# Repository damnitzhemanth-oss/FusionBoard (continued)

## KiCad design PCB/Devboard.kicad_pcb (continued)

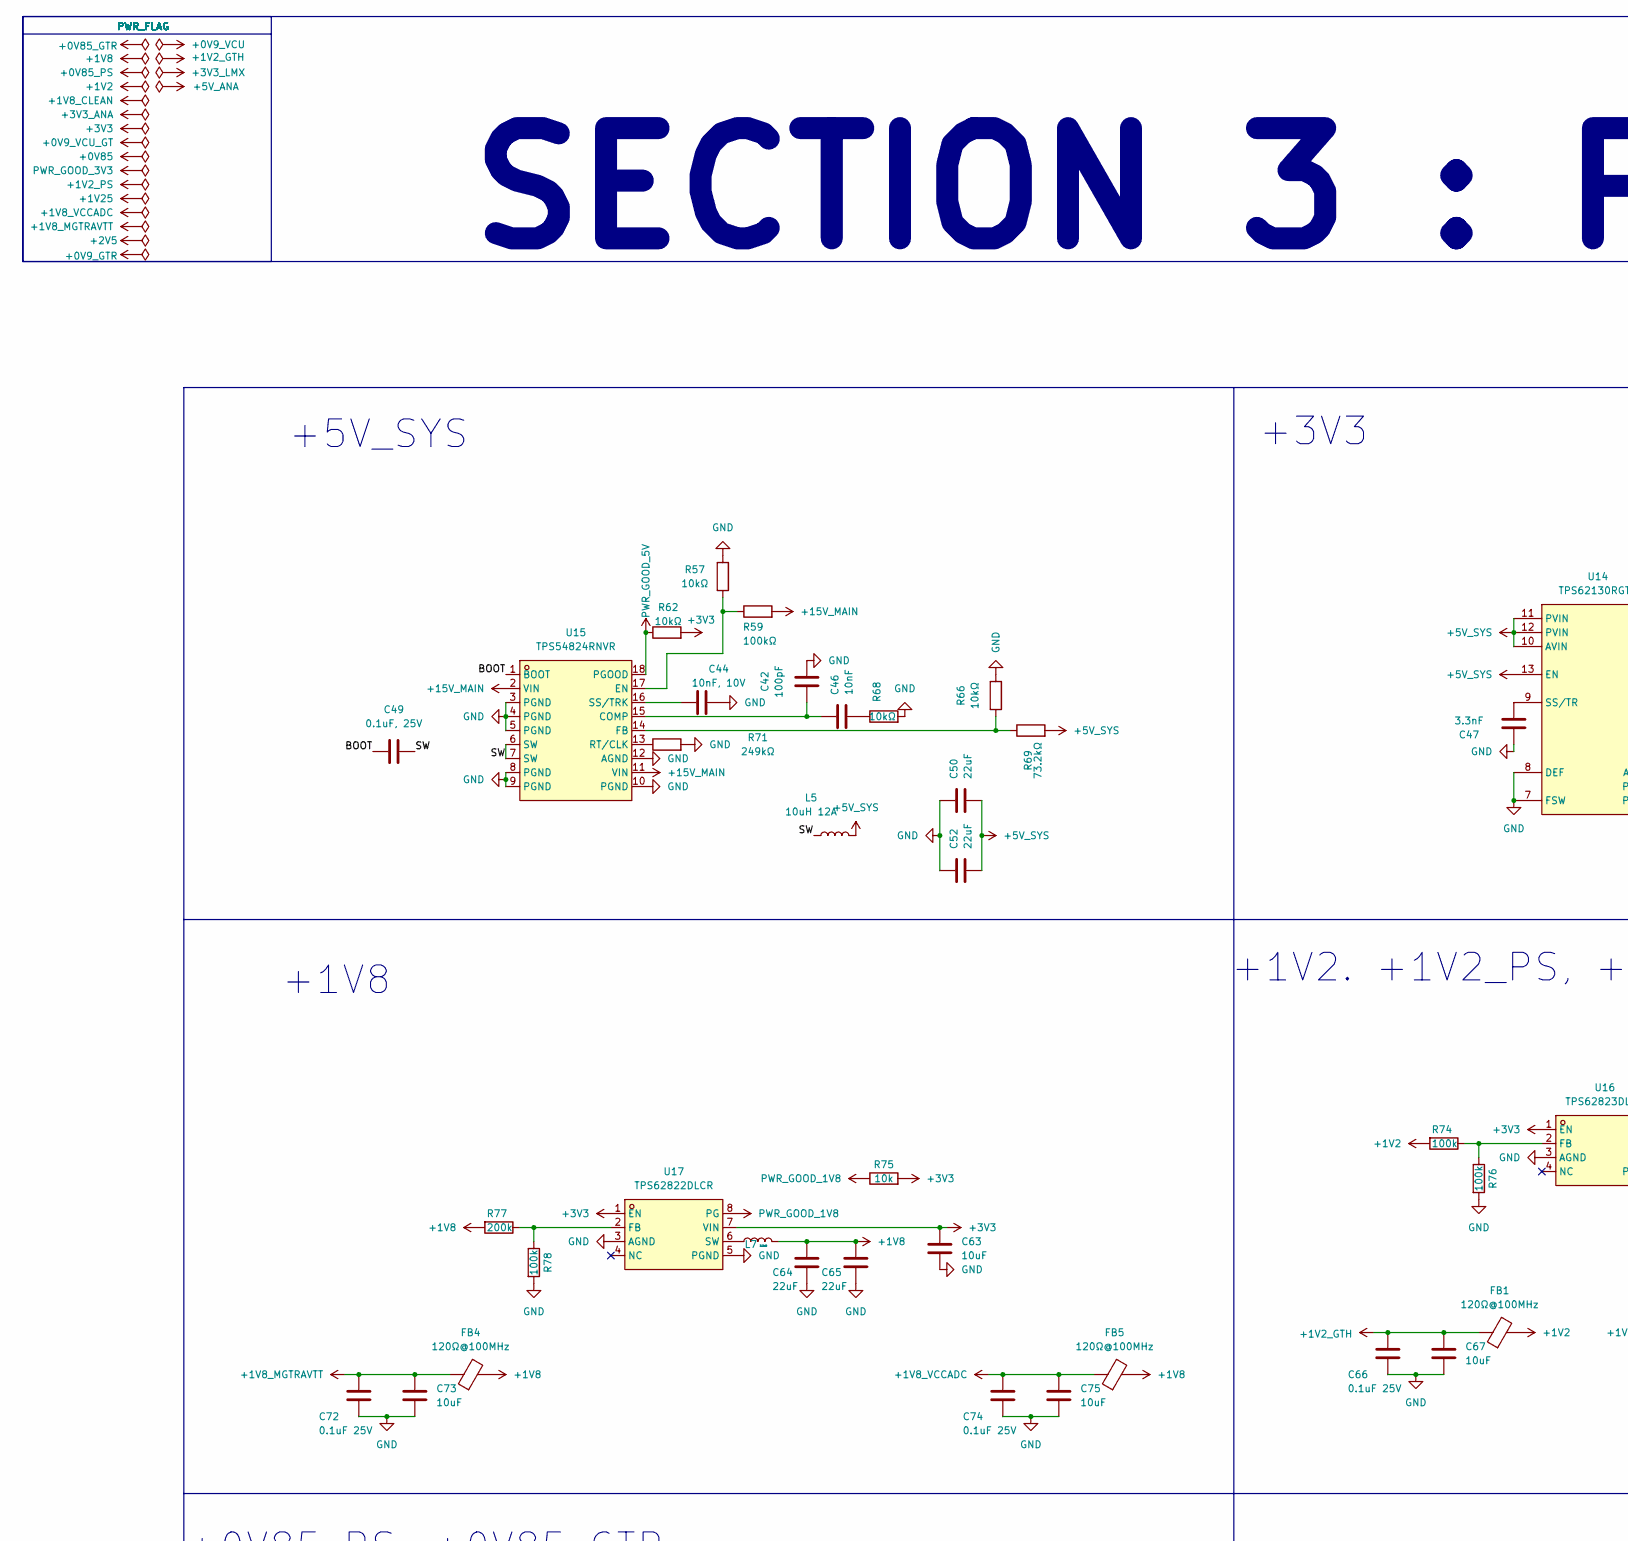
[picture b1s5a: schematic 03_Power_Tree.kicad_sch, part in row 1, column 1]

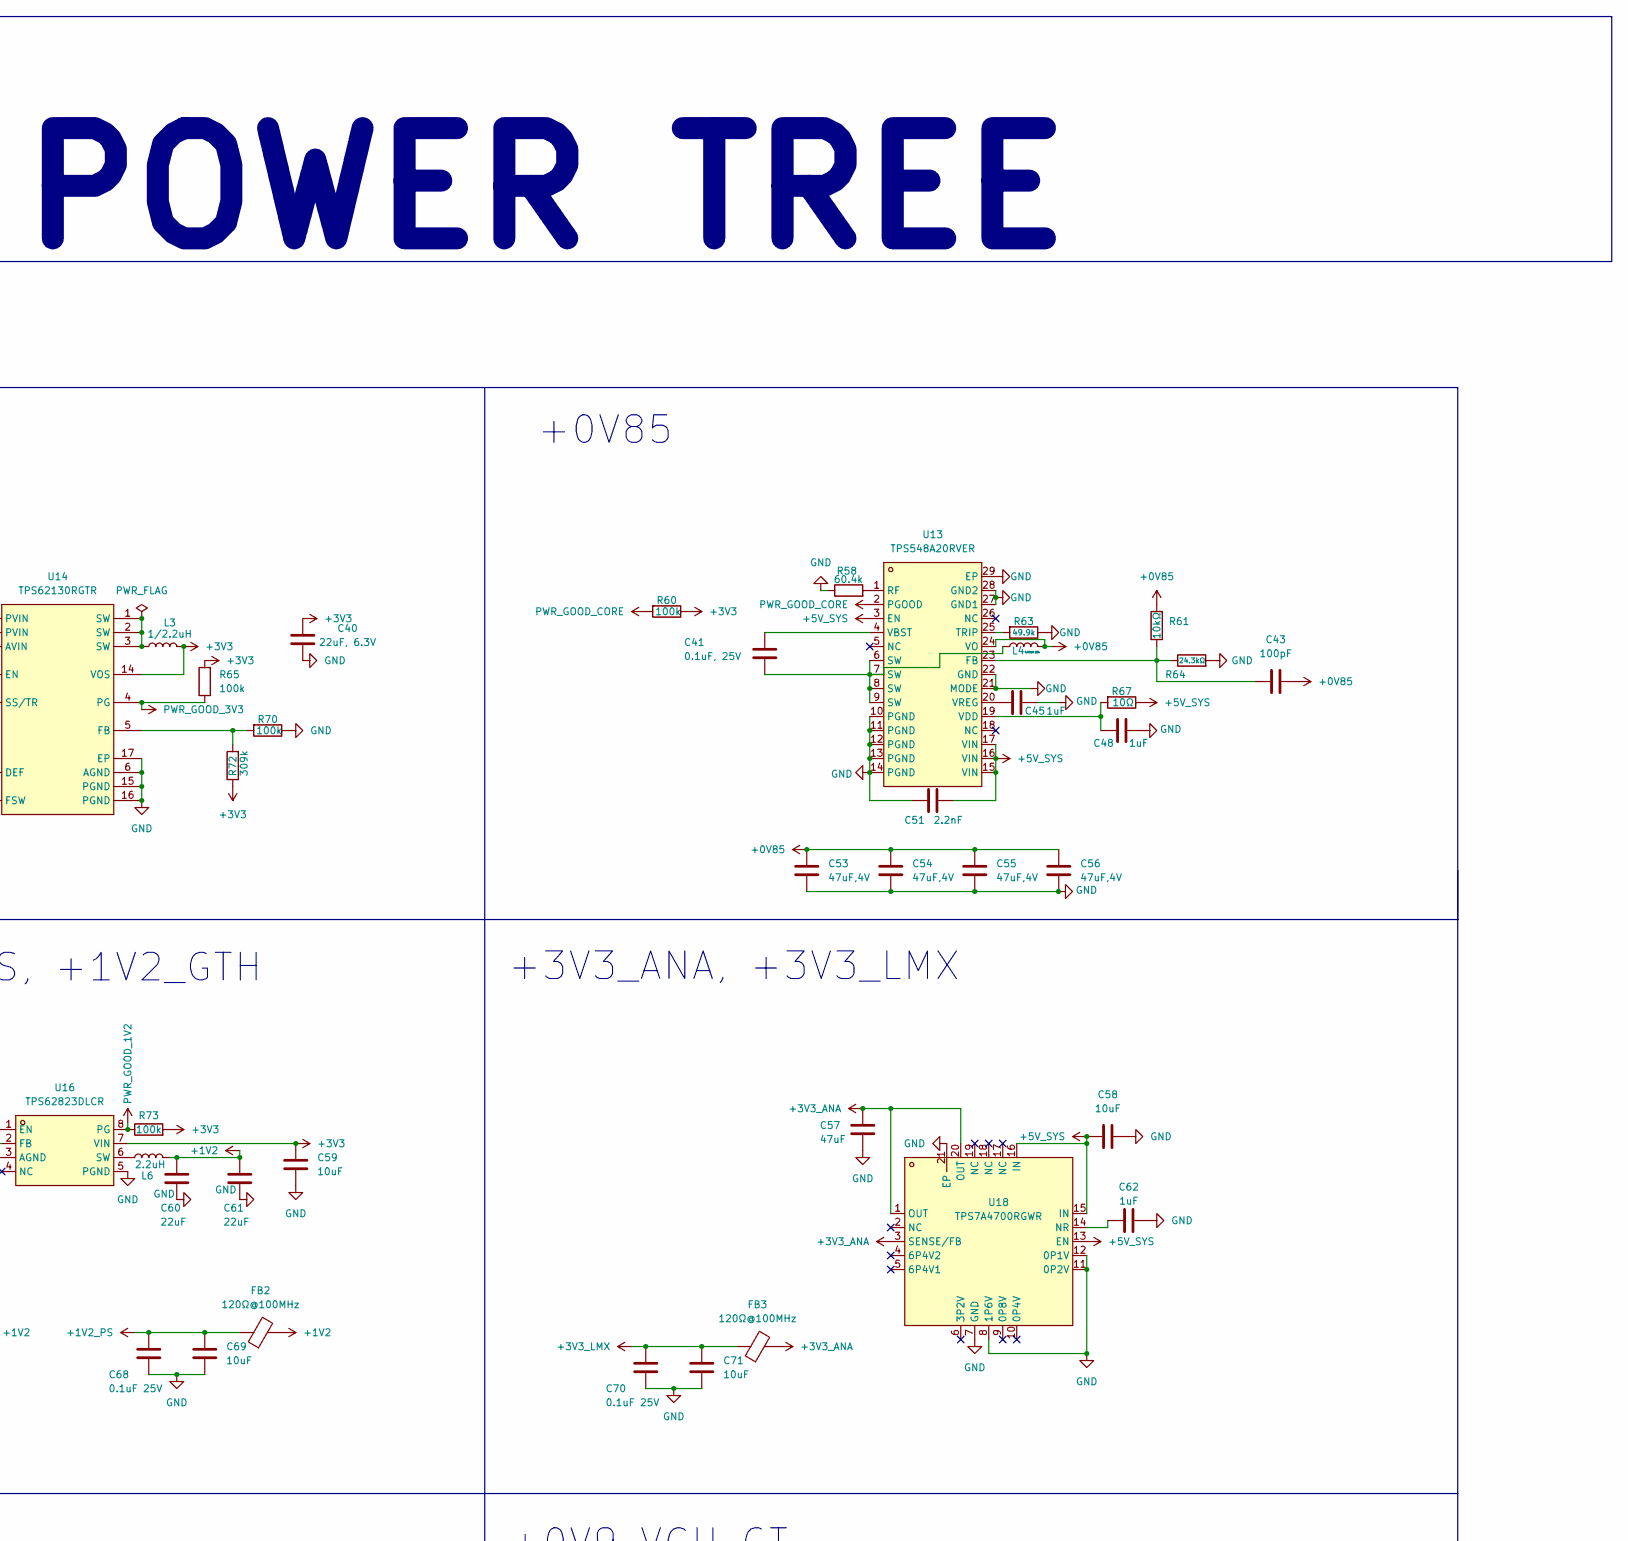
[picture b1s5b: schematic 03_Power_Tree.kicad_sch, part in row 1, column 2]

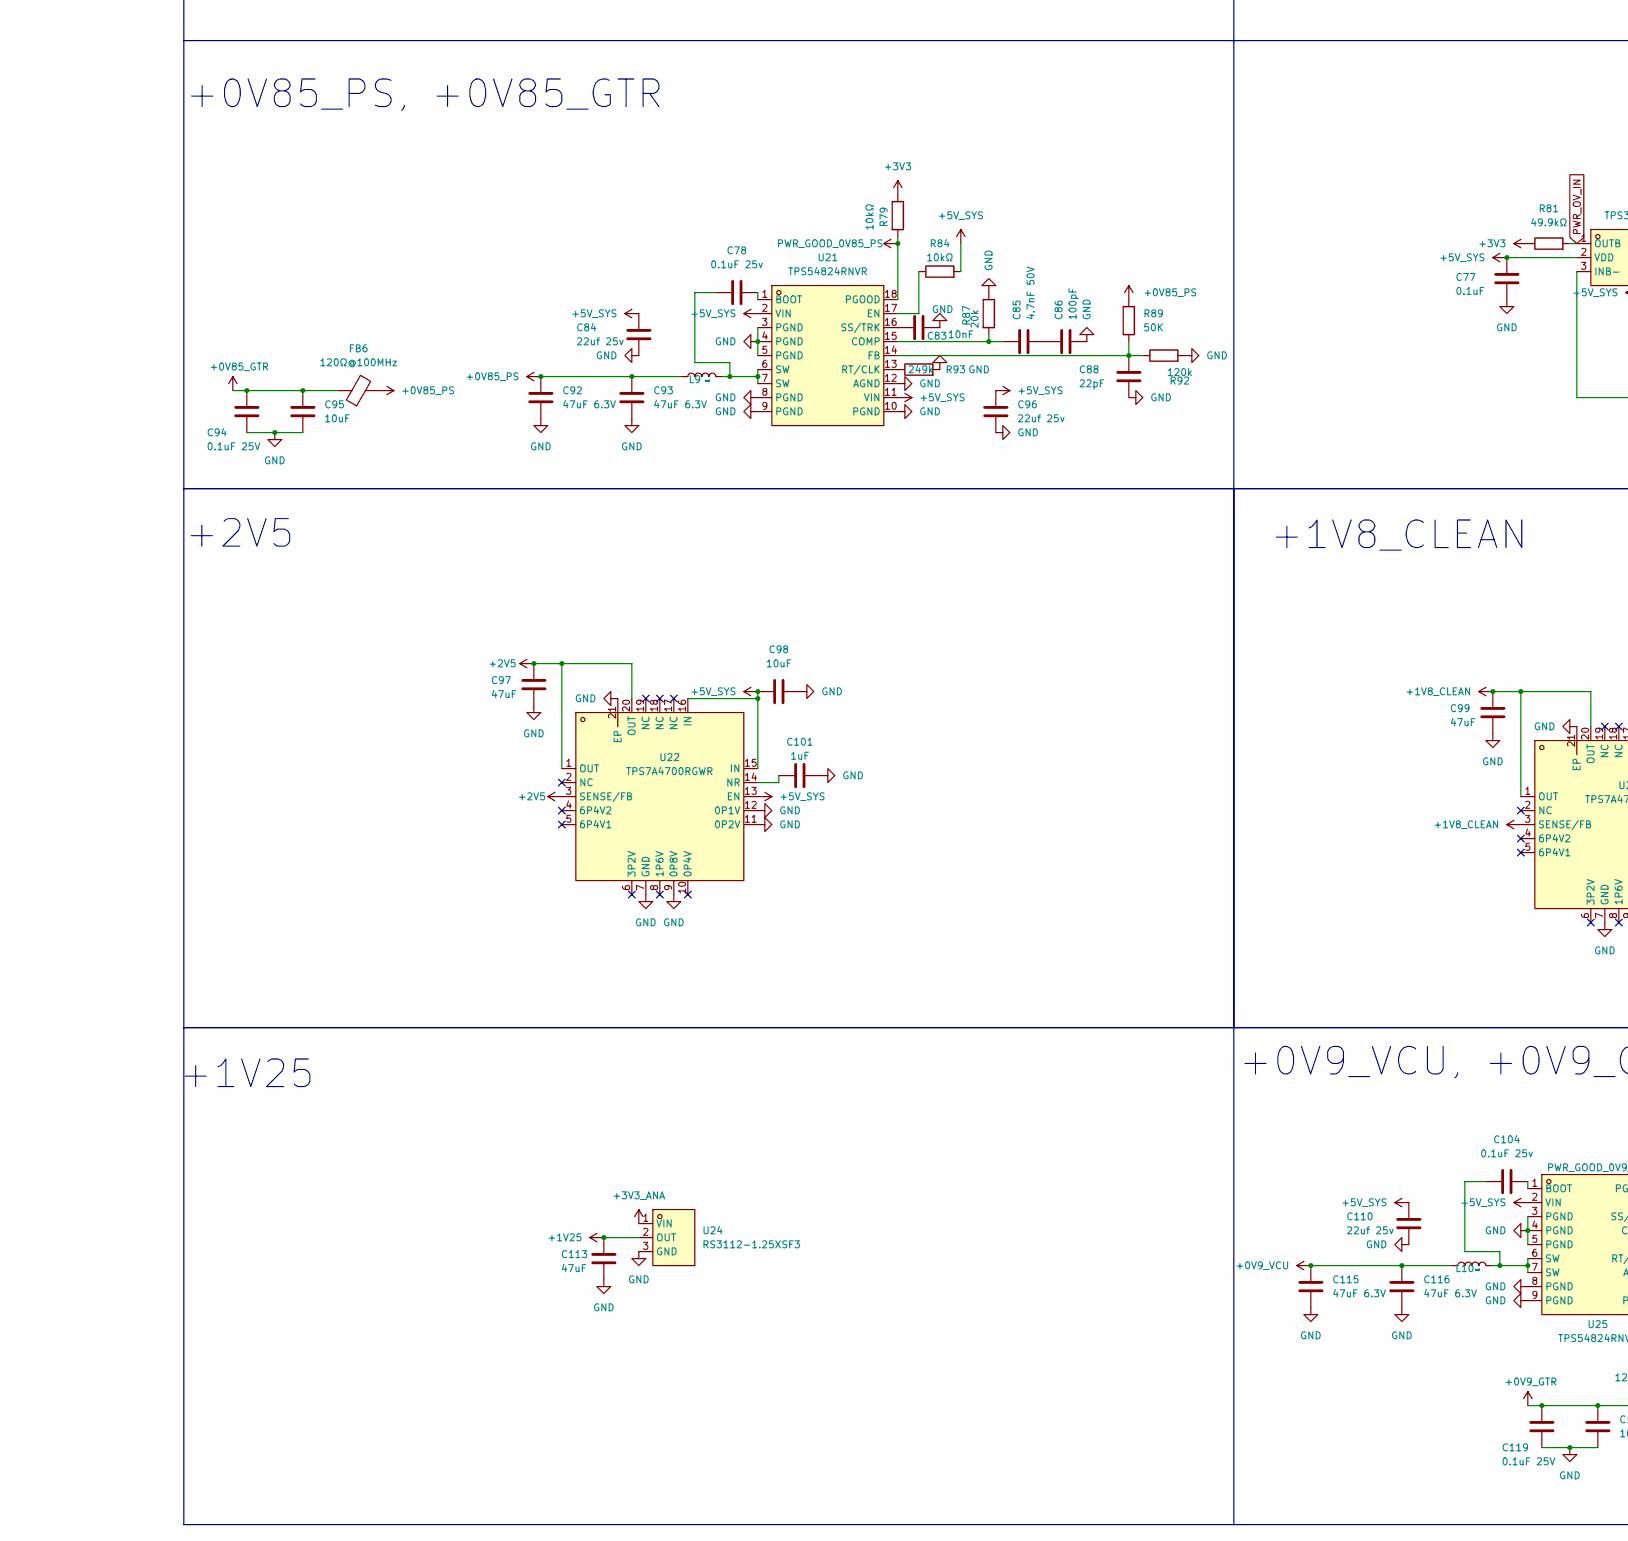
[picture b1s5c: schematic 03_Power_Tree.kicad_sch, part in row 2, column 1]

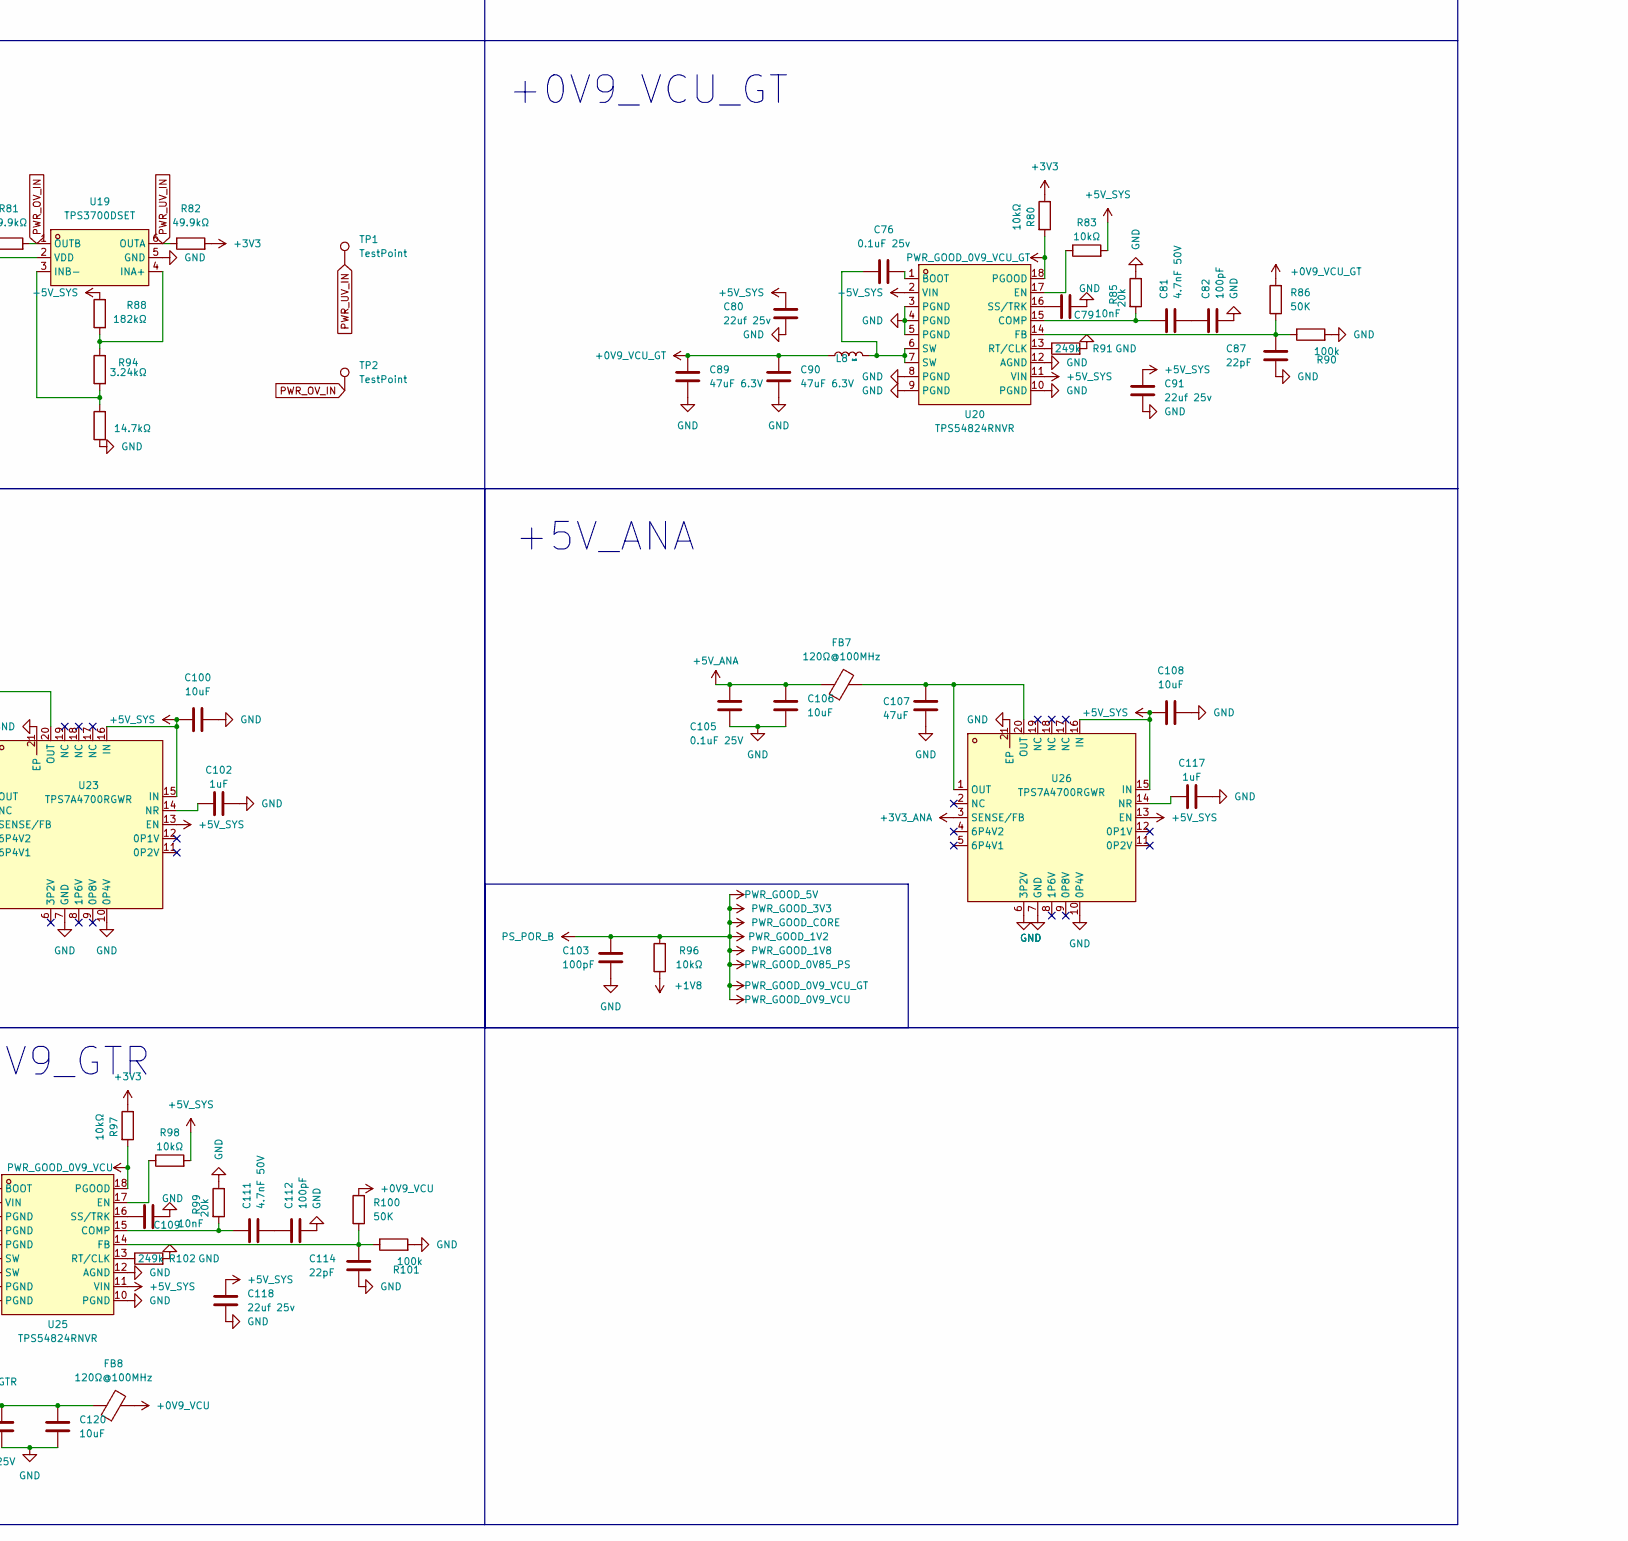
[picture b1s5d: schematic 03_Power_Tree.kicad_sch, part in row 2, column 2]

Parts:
C40: 22uF, 6.3V; C_0805_2012Metric
C41, C49: 0.1uF, 25V; C_0402_1005Metric
C42, C43, C82, C86, C103, C112: 100pF; C_0402_1005Metric
C44: 10nF, 10V; C_0402_1005Metric
C45, C48, C62, C101, C102, C117: 1uF; C_0402_1005Metric
C46, C79, C83, C109: 10nF; C_0402_1005Metric
C47: 3.3nF; C_0402_1005Metric
C50, C52, C60, C61, C64, C65: 22uF; C_0805_2012Metric
C51: 2.2nF; C_0402_1005Metric
C53, C54, C55, C56: 47uF,4V; C_1206_3216Metric
C57, C97, C99, C107, C113: 47uF; C_1206_3216Metric
C58, C59, C63, C67, C69, C71, C73, C75, C95, C98, C100, C106, C108, C120: 10uF; C_0402_1005Metric
C66, C68, C70, C72, C74, C94, C105, C119: 0.1uF 25V; C_0402_1005Metric
C76, C78, C104: 0.1uF 25v; C_0402_1005Metric
C77: 0.1uF; C_0402_1005Metric
C80, C84, C91, C96, C110, C118: 22uf 25v; C_0805_2012Metric
C81, C85, C111: 4.7nF 50V; C_0402_1005Metric
C87, C88, C114: 22pF; C_0402_1005Metric
C89, C90, C92, C93, C115, C116: 47uF 6.3V; C_1206_3216Metric
FB1, FB2, FB3, FB4, FB5, FB6, FB7, FB8: 120Ω@100MHz; L_01005_0402Metric
L3: 1/2.2uH; L_Bourns_SRP1245A
L4: 0.47uH 15A; L_Bourns_SRP1245A
L5: 10uH 12A; L_Bourns_SRP1245A
L6, L7: 2.2uH; L_Bourns_SRP1245A
L8, L9, L10: 1uH; L_Bourns_SRP1245A
R57, R61, R62, R66, R68, R79, R80, R83, R84, R96, R97, R98: 10kΩ; R_0402_1005Metric
R58: 60.4k; R_0402_1005Metric
R59: 100kΩ; R_0402_1005Metric
R60, R65, R70, R73, R74, R76, R78, R90, R101: 100k; R_0402_1005Metric
R63: 49.9k; R_0402_1005Metric
R64: 24.3kΩ; R_0402_1005Metric
R67: 10Ω; R_0402_1005Metric
R69: 73.2kΩ; R_0402_1005Metric
R71: 249kΩ; R_0402_1005Metric
R72: 309k; R_0402_1005Metric
R75: 10k; R_0402_1005Metric
R77: 200k; R_0402_1005Metric
R81, R82: 49.9kΩ; R_0402_1005Metric
R85, R87, R99: 20k; R_0402_1005Metric
R86, R89, R100: 50K; R_0402_1005Metric
R88: 182kΩ; R_0402_1005Metric
R91, R93, R102: 249k; R_0402_1005Metric
R92: 120k; R_0402_1005Metric
R94: 3.24kΩ; R_0402_1005Metric
R95: 14.7kΩ; R_0402_1005Metric
TP1, TP2: TestPoint; TestPoint_Pad_D1.0mm
U13: TPS548A20RVER; VQFN-CLIP-28_L4.5-W3.5-P0.40-BL-EP; MPN TPS548A20RVER; LCSC Part C468255
U14: TPS62130RGTR; QFN-16_L3.0-W3.0-P0.50-TL-EP1.7; MPN TPS62130RGTR; LCSC Part C43590
U15, U20, U21, U25: TPS54824RNVR; VQFN-18_L3.5-W3.5-P0.50-BL_TPS54824RNVR; MPN TPS54824RNVR; LCSC Part C2070614
U16: TPS62823DLCR; VSON-8_L2.0-W1.5-P0.50-BL; MPN TPS62823DLCR; LCSC Part C2693497
U17: TPS62822DLCR; VSON-8_L2.0-W1.5-P0.50-BL; MPN TPS62822DLCR; LCSC Part C473385
U18, U22, U23, U26: TPS7A4700RGWR; VQFN-20_L5.0-W5.0-P0.65-TL-EP; MPN TPS7A4700RGWR; LCSC Part C114839
U19: TPS3700DSET; WSON-6_L1.5-W1.5-P0.50-TL; MPN TPS3700DSET; LCSC Part C2869244
U24: RS3112-1.25XSF3; SOT-23-3_L2.9-W1.3-P0.95-LS2.4-BR; MPN RS3112-1.25XSF3; LCSC Part C19269195

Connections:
+0V9_GTR: C119.1, C120.2, FB8.1; also elsewhere on the board
+0V9_VCU: C115.1, C116.1, FB8.2, L10.1, R100.2; also elsewhere on the board
+0V9_VCU_GT: C89.1, C90.1, L8.1, R86.2; also elsewhere on the board
+0V85: C43.2, C53.1, C54.1, C55.1, C56.1, L4.2, R61.2, U13.24 (VO); also elsewhere on the board
+0V85_GTR: C94.1, C95.2, FB6.1; also elsewhere on the board
+0V85_PS: C92.1, C93.1, FB6.2, L9.1, R89.2; also elsewhere on the board
+1V2: C60.1, C61.1, FB1.2, FB2.2, L6.2, R74.2; also elsewhere on the board
+1V2_GTH: C66.1, C67.2, FB1.1; also elsewhere on the board
+1V2_PS: C68.1, C69.2, FB2.1; also elsewhere on the board
+1V8: C64.1, C65.1, FB4.2, FB5.2, L7.2, R77.2, R96.1; also elsewhere on the board
+1V8_CLEAN: C99.1, U23.1 (OUT), U23.3 (SENSE/FB), U23.20 (OUT); also elsewhere on the board
+1V8_MGTRAVTT: C72.1, C73.2, FB4.1; also elsewhere on the board
+1V8_VCCADC: C74.1, C75.2, FB5.1; also elsewhere on the board
+1V25: C113.1, U24.2 (OUT); also elsewhere on the board
+2V5: C97.1, U22.1 (OUT), U22.3 (SENSE/FB), U22.20 (OUT); also elsewhere on the board
+3V3: C40.1, C59.1, C63.1, L3.2, R60.1, R62.2, R65.2, R72.1, R73.2, R75.2, R79.1, R80.1, R81.1, R82.2, R97.1, U14.14 (VOS), U16.1 (EN), U16.7 (VIN), U17.1 (EN), U17.7 (VIN); also elsewhere on the board
+3V3_ANA: C57.1, FB3.2, U18.1 (OUT), U18.3 (SENSE/FB), U18.20 (OUT), U24.1 (VIN), U26.3 (SENSE/FB); also elsewhere on the board
+3V3_LMX: C70.1, C71.2, FB3.1; also elsewhere on the board
+5V_ANA: C105.1, C106.2, FB7.1; also elsewhere on the board
+5V_SYS: C50.2, C51.2, C52.2, C58.1, C77.1, C80.1, C84.1, C91.1, C96.1, C98.1, C100.1, C108.1, C110.1, C118.1, L5.2, R67.1, R69.2, R83.2, R84.2, R88.1, R98.2, U13.3 (EN), U13.15 (VIN), U13.16 (VIN), U13.17 (VIN), U14.10 (AVIN), U14.11 (PVIN), U14.12 (PVIN), U14.13 (EN), U18.13 (EN), U18.15 (IN), U18.16 (IN), U19.2 (VDD), U20.2 (VIN), U20.11 (VIN), U21.2 (VIN), U21.11 (VIN), U22.13 (EN), U22.15 (IN), U22.16 (IN), U23.13 (EN), U23.15 (IN), U23.16 (IN), U25.2 (VIN), U25.11 (VIN), U26.13 (EN), U26.15 (IN), U26.16 (IN); also elsewhere on the board
+15V_MAIN: R59.2, U15.2 (VIN), U15.11 (VIN); also elsewhere on the board
/Power Tree/BOOT: C49.1, U15.1 (BOOT)
/Power Tree/SW: C49.2, L5.1, U15.6 (SW), U15.7 (SW)
GND: C40.2, C42.2, C44.2, C45.2, C47.1, C48.2, C50.1, C51.1, C52.1, C53.2, C54.2, C55.2, C56.2, C57.2, C58.2, C59.2, C60.2, C61.2, C62.2, C63.2, C64.2, C65.2, C66.2, C67.1, C68.2, C69.1, C70.2, C71.1, C72.2, C73.1, C74.2, C75.1, C77.2, C79.2, C80.2, C82.2, C83.2, C84.2, C86.2, C87.2, C88.2, C89.2, C90.2, C91.2, C92.2, C93.2, C94.2, C95.1, C96.2, C97.2, C98.2, C99.2, C100.2, C101.2, C102.2, C103.1, C105.2, C106.1, C107.2, C108.2, C109.2, C110.2, C112.2, C113.2, C114.2, C115.2, C116.2, C117.2, C118.2, C119.2, C120.1, R57.2, R58.1, R63.1, R64.2, R66.2, R68.2, R70.1, R71.2, R76.2, R78.2, R85.1, R87.1, R90.2, R91.2, R92.2, R93.2, R95.2, R99.1, R101.2, R102.2, U13.10 (PGND), U13.11 (PGND), U13.12 (PGND), U13.13 (PGND), U13.14 (PGND), U13.21 (MODE), U13.22 (GND), U13.27 (GND1), U13.28 (GND2), U13.29 (EP), U14.6 (AGND), U14.7 (FSW), U14.8 (DEF), U14.15 (PGND), U14.16 (PGND), U14.17 (EP), U15.3 (PGND), U15.4 (PGND), U15.5 (PGND), U15.8 (PGND), U15.9 (PGND), U15.10 (PGND), U15.12 (AGND), U16.3 (AGND), U16.5 (PGND), U17.3 (AGND), U17.5 (PGND), U18.7 (GND), U18.8 (1P6V), U18.11 (0P2V), U18.12 (0P1V), U18.21 (EP), U19.5 (GND), U20.3 (PGND), U20.4 (PGND), U20.5 (PGND), U20.8 (PGND), U20.9 (PGND), U20.10 (PGND), U20.12 (AGND), U21.3 (PGND), U21.4 (PGND), U21.5 (PGND), U21.8 (PGND), U21.9 (PGND), U21.10 (PGND), U21.12 (AGND), U22.7 (GND), U22.9 (0P8V), U22.11 (0P2V), U22.12 (0P1V), U22.21 (EP), U23.7 (GND), U23.10 (0P4V), U23.21 (EP), U24.3 (GND), U25.3 (PGND), U25.4 (PGND), U25.5 (PGND), U25.8 (PGND), U25.9 (PGND), U25.10 (PGND), U25.12 (AGND), U26.6 (3P2V), U26.7 (GND), U26.10 (0P4V), U26.21 (EP); also elsewhere on the board
unnamed: C41.1, L4.1, U13.6 (SW), U13.7 (SW), U13.8 (SW), U13.9 (SW)
unnamed: C46.2, R68.1
unnamed: C76.1, L8.2, U20.6 (SW), U20.7 (SW)
unnamed: C78.1, L9.2, U21.6 (SW), U21.7 (SW)
unnamed: C81.2, C82.1
unnamed: C85.2, C86.1
unnamed: C104.1, L10.2, U25.6 (SW), U25.7 (SW)
unnamed: C107.1, FB7.2, U26.1 (OUT), U26.20 (OUT)
unnamed: C111.2, C112.1
unnamed: L3.1, U14.1 (SW), U14.2 (SW), U14.3 (SW)
unnamed: C43.1, R61.1, R64.1, U13.23 (FB)
unnamed: R58.2, U13.1 (RF)
unnamed: R63.2, U13.25 (TRIP)
unnamed: C41.2, U13.4 (VBST)
unnamed: C48.1, R67.2, U13.19 (VDD)
unnamed: C45.1, U13.20 (VREG)
unnamed: R70.2, R72.2, U14.5 (FB)
unnamed: C47.2, U14.9 (SS/TR)
unnamed: C42.1, C46.1, U15.15 (COMP)
unnamed: R57.1, R59.1, U15.17 (EN)
unnamed: R66.1, R69.1, U15.14 (FB)
unnamed: R71.1, U15.13 (RT/CLK)
unnamed: C44.1, U15.16 (SS/TRK)
unnamed: R74.1, R76.1, U16.2 (FB)
unnamed: L6.1, U16.6 (SW)
unnamed: R77.1, R78.1, U17.2 (FB)
unnamed: L7.1, U17.6 (SW)
unnamed: C62.1, U18.14 (NR)
unnamed: R88.2, R94.1, U19.4 (INA+)
unnamed: R94.2, R95.1, U19.3 (INB-)
unnamed: C76.2, U20.1 (BOOT)
unnamed: C81.1, R85.2, U20.15 (COMP)
unnamed: R83.1, U20.17 (EN)
unnamed: C87.1, R86.1, R90.1, U20.14 (FB)
unnamed: R91.1, U20.13 (RT/CLK)
unnamed: C79.1, U20.16 (SS/TRK)
unnamed: C78.2, U21.1 (BOOT)
unnamed: C85.1, R87.2, U21.15 (COMP)
unnamed: R84.1, U21.17 (EN)
unnamed: C88.1, R89.1, R92.1, U21.14 (FB)
unnamed: R93.1, U21.13 (RT/CLK)
unnamed: C83.1, U21.16 (SS/TRK)
unnamed: C101.1, U22.14 (NR)
unnamed: C102.1, U23.14 (NR)
unnamed: C104.2, U25.1 (BOOT)
unnamed: C111.1, R99.2, U25.15 (COMP)
unnamed: R98.1, U25.17 (EN)
unnamed: C114.1, R100.1, R101.1, U25.14 (FB)
unnamed: R102.1, U25.13 (RT/CLK)
unnamed: C109.1, U25.16 (SS/TRK)
unnamed: C117.1, U26.14 (NR)
PS_POR_B: C103.2, R60.2, R62.1, R65.1, R73.1, R75.1, R79.2, R80.2, R96.2, R97.2, U13.2 (PGOOD), U14.4 (PG), U15.18 (PGOOD), U16.8 (PG), U17.8 (PG), U20.18 (PGOOD), U21.18 (PGOOD), U25.18 (PGOOD); also elsewhere on the board
PWR_OV_IN: R81.2, TP2.1 (1_1), U19.1 (OUTB)
PWR_UV_IN: R82.1, TP1.1 (1_1), U19.6 (OUTA)

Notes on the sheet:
+1V8
+0V9_VCU, +0V9_GTR
+1V8_CLEAN
+3V3_ANA, +3V3_LMX
+1V25
+5V_SYS
+3V3
+0V85_PS, +0V85_GTR
SECTION 3 : POWER TREE
+1V2. +1V2_PS, +1V2_GTH
+0V85
+2V5
+0V9_VCU_GT
+5V_ANA

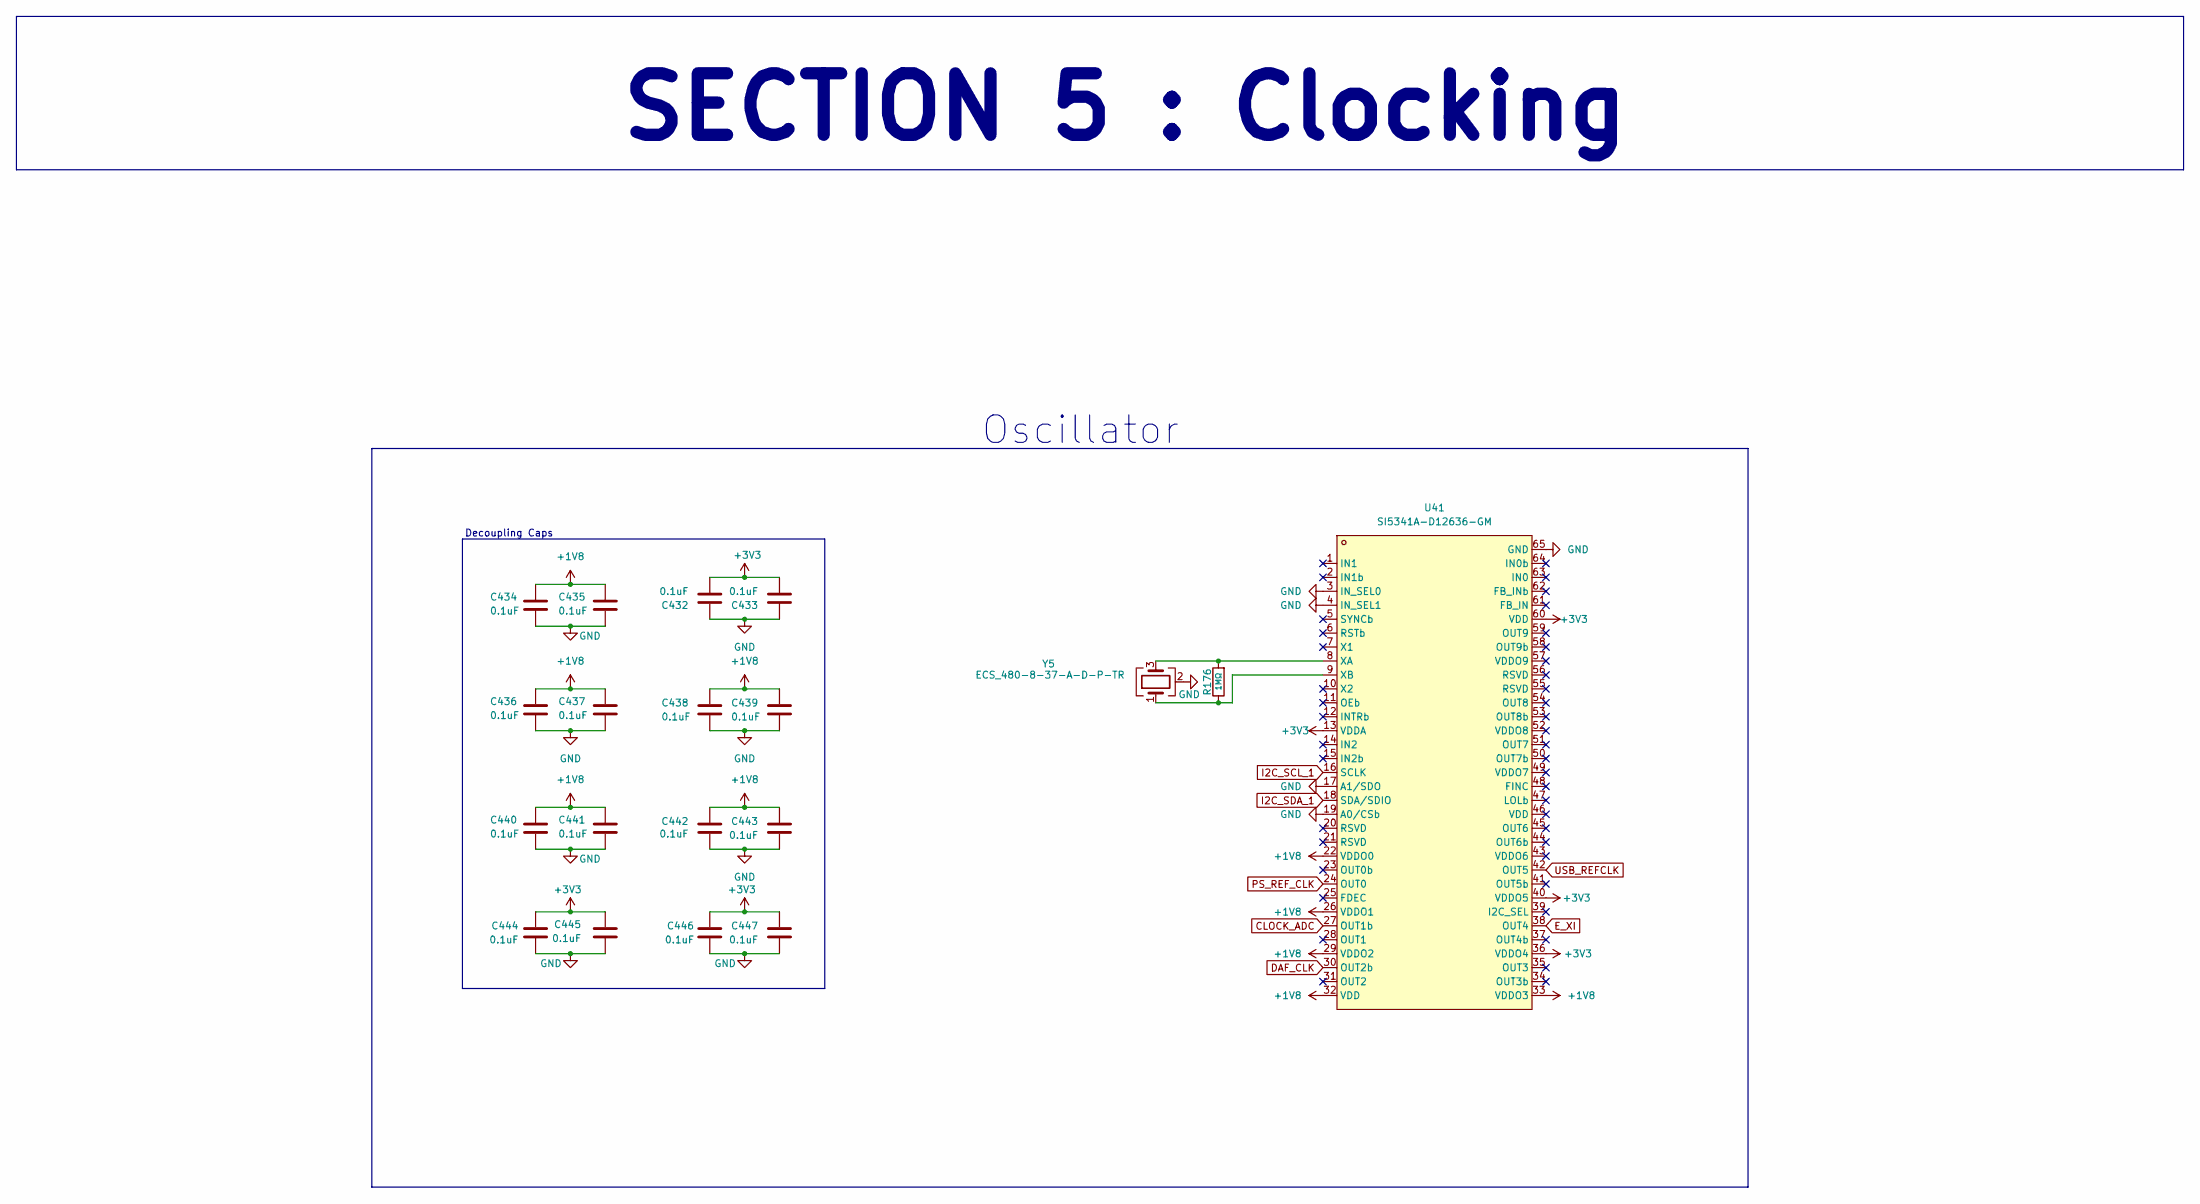
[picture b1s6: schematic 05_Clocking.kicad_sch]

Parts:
C432, C433, C434, C435, C436, C437, C438, C439, C440, C441, C442, C443, C444, C445, C446, C447: 0.1uF; C_0402_1005Metric
R176: 1MΩ; R_0402_1005Metric
U41: SI5341A-D12636-GM; QFN-64_L9.0-W9.0-P0.50-TL-EP5.2; MPN SI5341A-D12636-GM; LCSC Part C3609093
Y5: ECS_480-8-37-A-D-P-TR; Crystal_SMD_3225-4Pin_3.2x2.5mm

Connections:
+1V8: C434.1, C435.1, C436.1, C437.1, C438.1, C439.1, C440.1, C441.1, C442.1, C443.1, U41.22 (VDDO0), U41.26 (VDDO1), U41.29 (VDDO2), U41.32 (VDD), U41.33 (VDDO3); also elsewhere on the board
+3V3: C432.2, C433.2, C444.1, C445.1, C446.1, C447.1, U41.13 (VDDA), U41.36 (VDDO4), U41.40 (VDDO5), U41.60 (VDD); also elsewhere on the board
CLOCK_ADC: U41.27 (OUT1b); also elsewhere on the board
DAF_CLK: U41.30 (OUT2b); also elsewhere on the board
E_XI: U41.38 (OUT4); also elsewhere on the board
GND: C432.1, C433.1, C434.2, C435.2, C436.2, C437.2, C438.2, C439.2, C440.2, C441.2, C442.2, C443.2, C444.2, C445.2, C446.2, C447.2, U41.3 (IN_SEL0), U41.4 (IN_SEL1), U41.17 (A1/SDO), U41.19 (A0/CSb), U41.65 (GND), Y5.2 (G), Y5.4 (G); also elsewhere on the board
I2C_SCL_1: U41.16 (SCLK); also elsewhere on the board
I2C_SDA_1: U41.18 (SDA/SDIO); also elsewhere on the board
unnamed: R176.2, U41.8 (XA), Y5.3
unnamed: R176.1, U41.9 (XB), Y5.1
PS_REF_CLK: U41.24 (OUT0); also elsewhere on the board
USB_REFCLK: U41.42 (OUT5); also elsewhere on the board

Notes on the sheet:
Decoupling Caps
SECTION 5 : Clocking
Oscillator
